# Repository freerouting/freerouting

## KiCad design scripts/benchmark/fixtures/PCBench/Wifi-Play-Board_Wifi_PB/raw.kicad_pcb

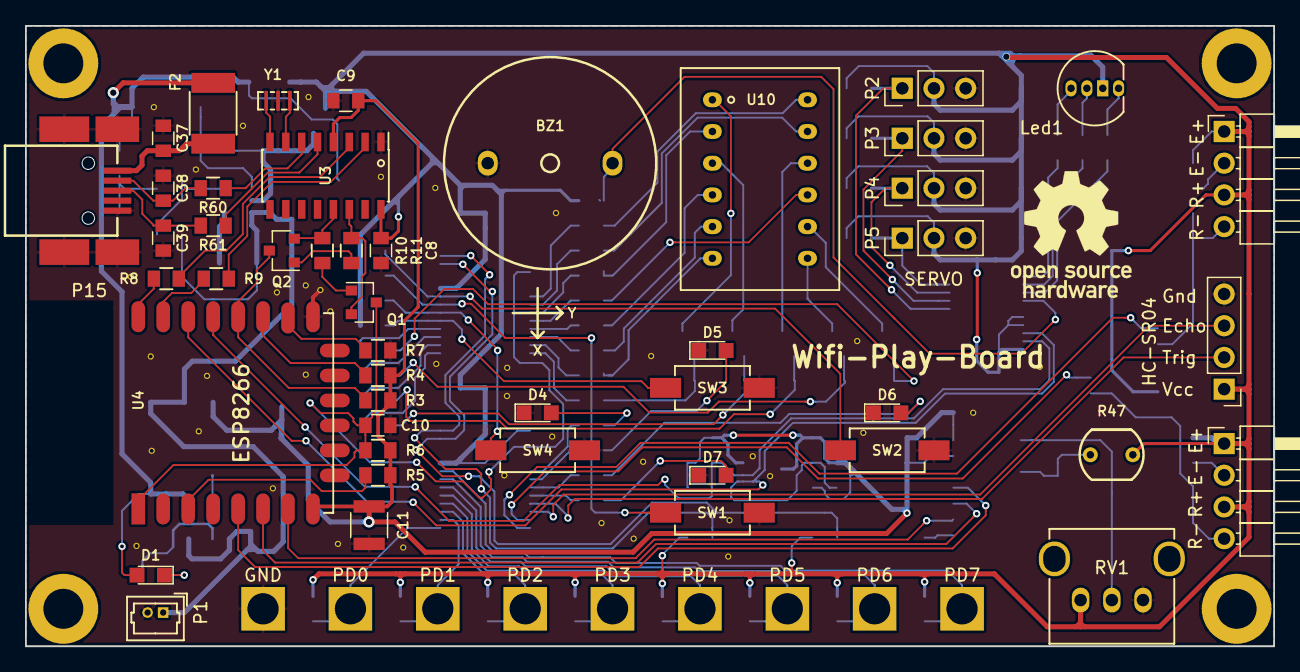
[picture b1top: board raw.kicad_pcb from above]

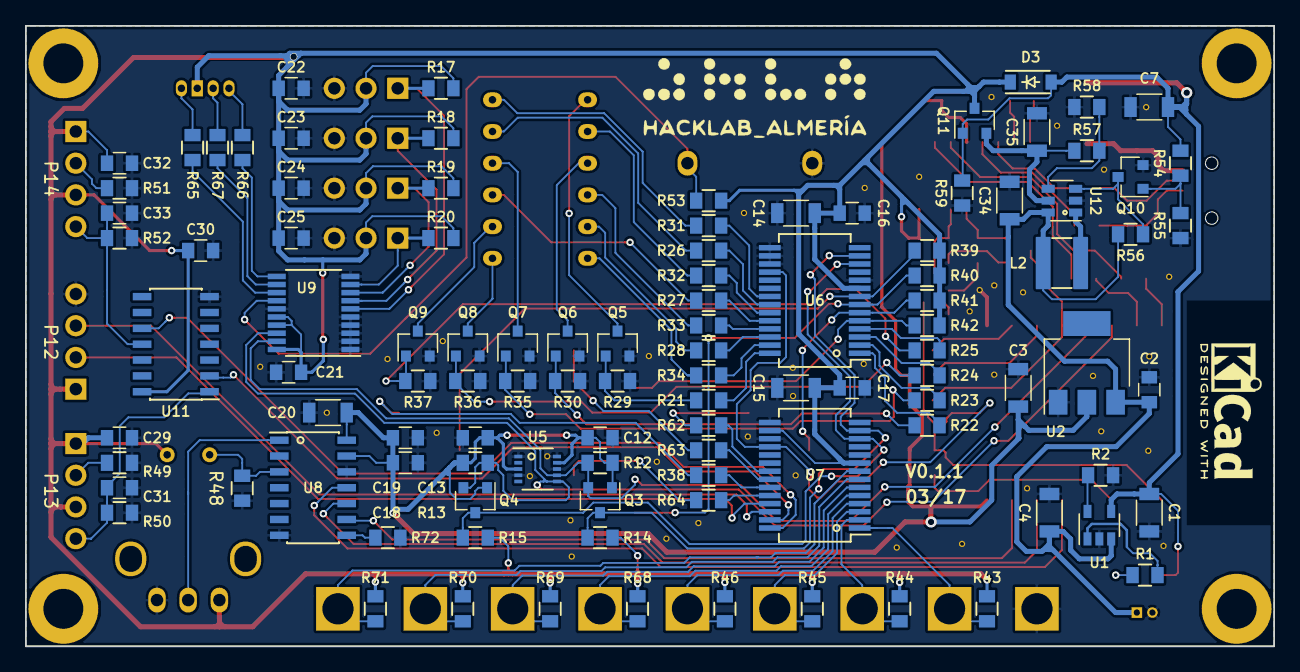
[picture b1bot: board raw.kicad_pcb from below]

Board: 2 copper layers, 100.0 x 49.7 mm, 200 parts (105 on the bottom side), 111 nets.

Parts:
BZ1: Buzzer; LOUDITY_LD-BZPN-1705
C1, C4, C14, C15, C20, C34: 4u7; C_1206
C2, C8, C9, C12, C13, C16, C17, C18, C19, C21, C29, C30, C32: 100n; C_0805
C3, C7, C35: 10u; C_1206
C10: 0.47n; C_0805
C11: 100u; C_1210
C22, C23, C24, C25: 1u; C_0805
C31, C33, C37: 10n; C_0805
C38, C39: 0,047n; C_0805
D1, D4, D5, D6, D7: LED; LED_0805
D3: MBR0520; SOD-123
F2: F; R_1812
Gnd-Via: VAL**; Gnd-Via
Gnd-Via#2, Gnd-Via#3, Gnd-Via#4, Gnd-Via#5, Gnd-Via#6, Gnd-Via#7, Gnd-Via#8, Gnd-Via#9, Gnd-Via#10, Gnd-Via#11, Gnd-Via#12, Gnd-Via#13, Gnd-Via#14, Gnd-Via#15, Gnd-Via#16, Gnd-Via#17, Gnd-Via#18, Gnd-Via#19, Gnd-Via#20, Gnd-Via#21, Gnd-Via#22, Gnd-Via#23, Gnd-Via#24, Gnd-Via#25, Gnd-Via#26, Gnd-Via#27, Gnd-Via#28, Gnd-Via#29, Gnd-Via#30, Gnd-Via#31, Gnd-Via#32, Gnd-Via#33, Gnd-Via#34, Gnd-Via#35, Gnd-Via#36, Gnd-Via#37, Gnd-Via#38, Gnd-Via#39: VAL**; Gnd-Via
L2: 4u7; BOURNS_SRN4012T
Led1: Led_RGB; LED_RGB_5mm_G_B_COM_R_Anodo_comun
P1: CONN_01X02; Molex_PicoBlade_53047-0210_02x1.25mm_Straight
P2, P3, P4, P5: CONN_01X03; Pin_Header_Straight_1x03_Pitch2.54mm
P6, P7, P8, P9, P10, P16, P17, P18, P19: CONN_01X01; Pad_Conector_Cocodrilo
P12: CONN_01X04; Socket_Strip_Straight_1x04_Pitch2.54mm
P13, P14: CONN_01X04; Pin_Header_Angled_1x04_Pitch2.54mm
P15: USB_MINI; usb_mini_molex_675031020
Q1, Q2, Q5, Q6, Q7, Q8, Q9: SMBT3904; SOT-23
Q3, Q4: BSS138; SOT-23
Q10: BC849; SOT-23
Q11: NX2301P; SOT-23
R1, R2, R8, R9: 470; R_0805
R3, R4, R5, R6, R7, R10, R11, R17, R18, R19, R20, R39, R40, R41, R42, R53, R56, R59: 10K; R_0805
R12, R13, R14, R15: 4K7; R_0805
R21, R22, R23, R24, R25, R48, R54: 1K; R_0805
R26, R27, R28, R31, R32, R33, R34, R65, R66, R67: 120; R_0805
R29, R30, R35, R36, R37, R50, R52, R55, R72: 47K; R_0805
R38, R62, R63, R64: 220; R_0805
R43, R44, R45, R46, R68, R69, R70, R71: 10M; R_0805
R47: LDR; LDR_TOKEN_PGM5_Series
R49, R51: 220R; R_0805
R57: 976K; R_0805
R58: 309K; R_0805
R60, R61: 22R; R_0805
RV1: POT; ALP_RK09K111
SW1, SW2, SW3, SW4: Pulsador_2p; CANAL_ELECTRONIC_DTSM-31N-B
U1: MCP73831T; SOT-23-5
U2: LD1117S33TR; SOT-223
U3: CH340G; SOIC-16_3.9x9.9mm_Pitch1.27mm
U4: ESP8266; ESP-12E
U5: MMA7660FC; DFN-10-1EP_3x3mm_Pitch0.5mm
U6, U7: MCP23017; SSOP-28_5.3x10.2mm_Pitch0.65mm
U8: MCP3204; SOIC-14_3.9x8.7mm_Pitch1.27mm
U9: PCA9634; TSSOP-20_4.4x6.5mm_Pitch0.65mm
U10: Matriz_5x7_Anodo_Filas; Matriz_Led_7X5
U11: 40106; SOIC-14_3.9x8.7mm_Pitch1.27mm
U12: MCP1640; SOT-23-6
Y1: Cristal; Murata_CSTCE_V_A

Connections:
+3V3: C3.1, C9.1, C11.1, C12.1, C13.1, C18.1, C19.1, C20.1, Q3.1, Q4.1, R3.2, R4.2, R5.2, R6.2, R12.1, R13.1, U2.2, U3.4, U4.8, U5.3, U5.9, U8.13, U8.14
+5V: C8.1, C14.1, C15.1, C16.1, C17.1, C21.1, C22.1, C23.1, C24.1, C25.1, C29.1, C30.1, C32.1, D3.1, Led1.3, P2.2, P3.2, P4.2, P5.2, P12.1, P13.1, P13.3, P14.1, P14.3, Q11.3, R14.1, R15.1, R17.1, R18.1, R19.1, R20.1, R39.1, R40.1, R41.1, R42.1, R43.1, R44.1, R45.1, R46.1, R47.1, R53.1, R68.1, R69.1, R70.1, R71.1, RV1.1, U3.16, U6.9, U7.9, U7.16, U9.16, U9.17, U9.20, U11.14
/Control/EN: R5.1, U4.3
/Control/GPIO0: Q2.3, R3.1, U4.18
/Control/GPIO2: R4.1, U4.17
/Control/GPIO15: R7.1, U4.16
/Control/RxD: R9.1, U4.21
/Control/TxD: R8.1, U4.22
/Control/USBD+: R61.1, U3.5
/Control/USBD-: R60.1, U3.6
BUZZER: BZ1.1, R53.2, U9.14
CH0: RV1.2, U8.1
CH2: R47.2, R48.2, U8.3
GND: BZ1.2, C1.2, C2.2, C3.2, C4.2, C7.2, C8.2, C9.2, C10.2, C11.2, C12.2, C13.2, C14.2, C15.2, C16.2, C17.2, C18.2, C19.2, C20.2, C21.2, C22.2, C23.2, C24.2, C25.2, C29.2, C30.2, C31.2, C32.2, C33.2, C34.2, C35.2, C37.2, C38.2, C39.2, D4.1, D5.1, D6.1, D7.1, Gnd-Via.1, Gnd-Via#2.1, Gnd-Via#3.1, Gnd-Via#4.1, Gnd-Via#5.1, Gnd-Via#6.1, Gnd-Via#7.1, Gnd-Via#8.1, Gnd-Via#9.1, Gnd-Via#10.1, Gnd-Via#11.1, Gnd-Via#12.1, Gnd-Via#13.1, Gnd-Via#14.1, Gnd-Via#15.1, Gnd-Via#16.1, Gnd-Via#17.1, Gnd-Via#18.1, Gnd-Via#19.1, Gnd-Via#20.1, Gnd-Via#21.1, Gnd-Via#22.1, Gnd-Via#23.1, Gnd-Via#24.1, Gnd-Via#25.1, Gnd-Via#26.1, Gnd-Via#27.1, Gnd-Via#28.1, Gnd-Via#29.1, Gnd-Via#30.1, Gnd-Via#31.1, Gnd-Via#32.1, Gnd-Via#33.1, Gnd-Via#34.1, Gnd-Via#35.1, Gnd-Via#36.1, Gnd-Via#37.1, Gnd-Via#38.1, Gnd-Via#39.1, P1.2, P2.3, P3.3, P4.3, P5.3, P10.1, P12.4, P15.5, P15.6, Q5.2, Q6.2, Q7.2, Q8.2, Q9.2, Q10.2, R2.2, R7.2, R29.2, R30.2, R35.2, R36.2, R37.2, R48.1, R49.2, R50.2, R51.2, R52.2, R55.2, R58.2, R59.1, R72.2, RV1.3, SW1.1, SW2.1, SW3.1, SW4.1, U1.2, U2.1, U3.1, U4.15, U5.1, U5.4, U5.8, U5.10, U6.10, U6.15, U6.16, U6.17, U7.10, U7.15, U7.17, U8.7, U8.12, U9.1, U9.2, U9.3, U9.4, U9.5, U9.10, U9.15, U11.7, U12.2, Y1.2
LED_BLUE: R67.2, U9.12
LED_GREEN: R66.2, U9.11
LED_RED: R65.2, U9.13
MISO: U4.6, U8.10
MOSI: U4.7, U8.9
unnamed: C31.1, P13.4, R50.1, U11.1
unnamed: C33.1, P14.4, R52.1, U11.11
unnamed: C37.1, F2.2, P15.1
unnamed: C38.1, P15.2, R60.2
unnamed: C39.1, P15.3, R61.2
unnamed: D1.1, R1.2
unnamed: D4.2, R62.2
unnamed: D5.2, R63.2
unnamed: D6.2, R38.2
unnamed: D7.2, R64.2
unnamed: L2.2, U12.1
unnamed: Led1.1, R66.1
unnamed: Led1.2, R67.1
unnamed: Led1.4, R65.1
unnamed: P13.2, R49.1
unnamed: P14.2, R51.1
unnamed: Q1.1, R10.1
unnamed: Q1.2, R11.2, U3.14
unnamed: Q2.1, R11.1
unnamed: Q2.2, R10.2, U3.13
unnamed: Q5.1, R21.1, R29.1
unnamed: Q5.3, U10.1
unnamed: Q6.1, R22.1, R30.1
unnamed: Q6.3, U10.3
unnamed: Q7.1, R23.1, R35.1
unnamed: Q7.3, U10.10
unnamed: Q8.1, R24.1, R36.1
unnamed: Q8.3, U10.7
unnamed: Q9.1, R25.1, R37.1
unnamed: Q9.3, U10.8
unnamed: Q10.1, R54.1, R55.1
unnamed: Q10.3, R56.1, U12.3
unnamed: R1.1, U1.1
unnamed: R2.1, U1.5
unnamed: R8.2, U3.3
unnamed: R9.2, U3.2
unnamed: R26.1, U10.11
unnamed: R27.1, U10.9
unnamed: R28.1, U10.5
unnamed: R31.1, U10.12
unnamed: R32.1, U10.2
unnamed: R33.1, U10.4
unnamed: R34.1, U10.6
unnamed: R57.2, R58.1, U12.4
unnamed: R72.1, U8.8
unnamed: U3.7, Y1.1
unnamed: U3.8, Y1.3
PA0: R31.2, U6.21
PA1: R26.2, U6.22
PA2: R32.2, U6.23
PA3: R27.2, U6.24
PA4: R33.2, U6.25
PA5: R28.2, U6.26
PA6: R34.2, U6.27
PA7: R21.2, U6.28
PB0: R22.2, U6.1
PB1: R23.2, U6.2
PB2: R24.2, U6.3
PB3: R25.2, U6.4
PB4: R42.2, SW3.2, U6.5
PB5: R41.2, SW4.2, U6.6
PB6: R40.2, SW1.2, U6.7
PB7: R39.2, SW2.2, U6.8
PC0: R62.1, U7.21
PC1: R63.1, U7.22
PC2: R38.1, U7.23
PC3: R64.1, U7.24
PC4: P12.2, U7.25
PC5: P12.3, U7.26
PC6: U7.27, U11.2
PC7: U7.28, U11.10
PD0: P6.1, R43.2, U7.1
PD1: P7.1, R44.2, U7.2
PD2: P8.1, R45.2, U7.3
PD3: P9.1, R46.2, U7.4
PD4: P16.1, R68.2, U7.5
PD5: P17.1, R69.2, U7.6
PD6: P18.1, R70.2, U7.7
PD7: P19.1, R71.2, U7.8
SCK: U4.5, U8.11
SCL: Q4.2, R13.2, U4.20, U5.6, U9.18
SCL2: Q4.3, R15.2, U6.12, U7.12
SDA: Q3.2, R12.2, U4.19, U5.7, U9.19
SDA2: Q3.3, R14.2, U6.13, U7.13
SERVO1: P2.1, R17.2, U9.6
SERVO2: P3.1, R18.2, U9.7
SERVO3: P4.1, R19.2, U9.8
SERVO4: P5.1, R20.2, U9.9
V5VBOOST: C35.1, Q11.2, R57.1, U12.5
VBATT: C2.1, C4.1, C34.1, L2.1, P1.1, R56.2, U1.3, U2.3, U12.6
VUSB: C1.1, C7.1, D1.2, D3.2, F2.1, Q11.1, R54.2, R59.2, U1.4
~RESET: C10.1, Q1.3, R6.1, U4.1, U6.18, U7.18

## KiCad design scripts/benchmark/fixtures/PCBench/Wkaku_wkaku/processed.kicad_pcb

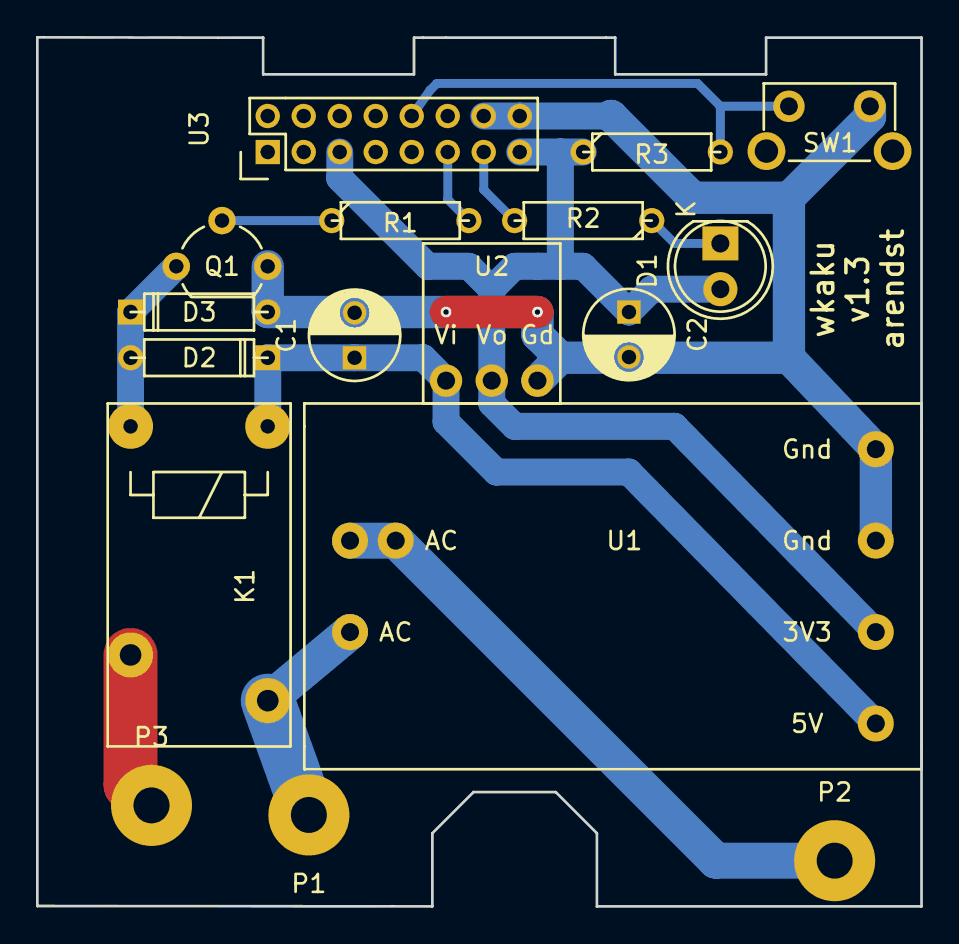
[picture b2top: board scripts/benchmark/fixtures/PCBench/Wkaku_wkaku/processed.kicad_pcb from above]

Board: 2 copper layers, 49.1 x 48.3 mm, 17 parts (0 on the bottom side), 12 nets.

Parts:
C1, C2: 100uF; C_Radial_D5_L11_P2.5
D1: LED; LED-5MM
D2, D3: 1N4007; D3
K1: RELAY_SPST; Relay_SPST
P1: Li; SolderWirePad_single_2mmDrill
P2: N; SolderWirePad_single_2mmDrill
P3: Lo; SolderWirePad_single_2mmDrill
Q1: BC547; TO-92_Molded_Wide
R1, R2: 1k; R3
R3: 10k; R3
SW1: SPST; SW_Tactile_SPST_Angled
U1: ACDC_Opt2; ACDC_Options
U2: AMS1117
U3: ESP-12E; ESP-12_Pitch2.00mm

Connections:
+3V3: C2.1, D1.2, R3.1, U1.4, U2.2, U3.3, U3.8
+5V: C1.1, D2.1, K1.A1, U1.3, U2.3
/BUTTON: R3.2, SW1.1, U3.18
/LED: R2.2, U3.7
/LIFE: K1.7, P1.1, U1.1
/RELAY: R1.2, U3.6
GND: C1.2, C2.2, D3.2, Q1.3, SW1.2, U1.5, U1.6, U2.1, U3.15, U3.16
unnamed: D1.1, R2.1
unnamed: D2.2, D3.1, K1.A2, Q1.1
unnamed: K1.5, P3.1
unnamed: P2.1, U1.2, U1.7
unnamed: Q1.2, R1.1

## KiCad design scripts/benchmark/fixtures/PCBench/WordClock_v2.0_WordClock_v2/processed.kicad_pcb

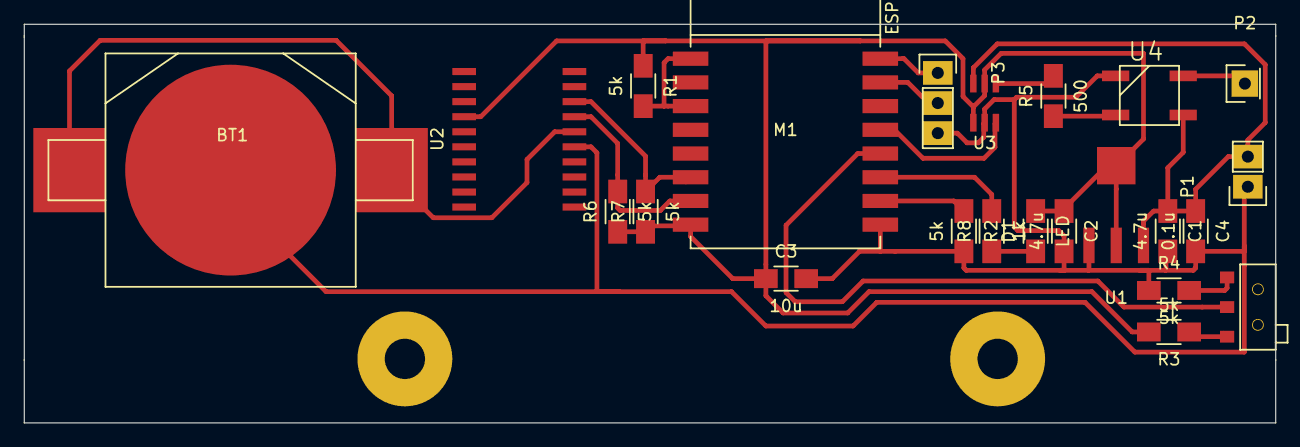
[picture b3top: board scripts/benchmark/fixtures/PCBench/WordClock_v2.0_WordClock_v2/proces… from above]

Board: 2 copper layers, 105.5 x 33.6 mm, 23 parts (0 on the bottom side), 19 nets.

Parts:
BT1: Battery; Battery_Holder_Cell_20mm_smd
C1, C2: 4.7u; C_1206_HandSoldering_IainEdit
C3: 10u; C_1206_HandSoldering_IainEdit
C4: 0.1u; C_1206_HandSoldering_IainEdit
D1: LED; C_1206_HandSoldering_IainEdit
M1: ESP-07
P1: 5V_input; Socket_Strip_Straight_1x02
P2: WS2812b_Out; Socket_Strip_Straight_1x01
P3: UART; Socket_Strip_Straight_1x03_IainEdit
R1, R2, R3, R4, R6, R7: 5k; C_1206_HandSoldering_IainEdit
R5: 500; C_1206_HandSoldering_IainEdit
R8: 1k; C_1206_HandSoldering_IainEdit
SW1: SWITCH_INV; SlideSwitch_smd
U1: NCP1117ST33T3G; SOT223_HandSolder
U2: DS3232; Maxim_SOIC-20_W20-H2
U3: SN74LVC1T45; TI-DBV-SOT23_handsolder
U4: WS2812b; WS2812b_handsolder

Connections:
+3V3: C2.1, C3.1, D1.2, M1.8, R1.1, R3.2, R6.1, R7.1, U1.2, U2.4, U3.1, U3.5
+5VD: C1.1, C4.1, P1.2, U1.3, U3.6, U4.1
GND: BT1.2, C1.2, C2.2, C3.2, C4.2, M1.9, P1.1, P3.3, R2.2, R4.1, U1.1, U2.15, U3.2, U4.3
GPIO0: M1.12, SW1.2
LED: M1.11, R8.2
unnamed: BT1.1, U2.16
unnamed: D1.1, R8.1
unnamed: M1.1, M1.3, R1.2
unnamed: M1.10, R2.1
unnamed: P2.1, U4.2
unnamed: R3.1, SW1.1
unnamed: R4.2, SW1.3
unnamed: R5.1, U4.4
unnamed: R5.2, U3.4
SCL: M1.6, R7.2, U2.18
SDA: M1.7, R6.2, U2.17
UART_Rx: M1.15, P3.2
UART_Tx: M1.16, P3.1
WS2812b_In: M1.13, U3.3

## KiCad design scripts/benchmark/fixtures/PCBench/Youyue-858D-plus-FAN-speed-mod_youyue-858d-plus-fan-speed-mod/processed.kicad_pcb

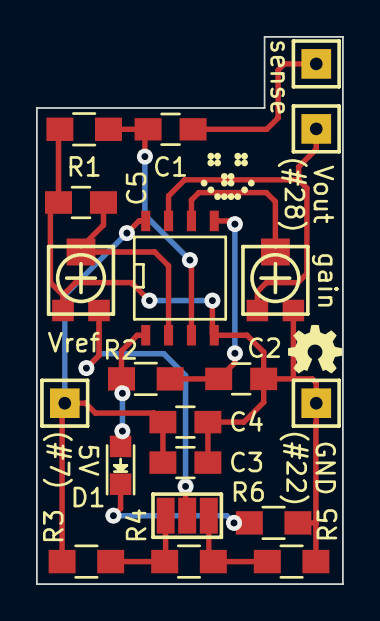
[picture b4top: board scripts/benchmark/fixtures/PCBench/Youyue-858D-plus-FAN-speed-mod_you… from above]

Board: 2 copper layers, 17.0 x 30.4 mm, 20 parts (0 on the bottom side), 13 nets.

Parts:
C1, C3: 100n; C_0805_HandSoldering
C2: 1µF; C_0805_HandSoldering
C4, C5: 1µ; C_0805_HandSoldering
D1: LED; LED-0805
JP1: SMD-JUMPER3; SMD-solder-bridge-3pin
P1, P2, P3, P4: CONN_01X01; SIL-1
R1: 1M; R_0805_HandSoldering
R2: 100k; R_0805_HandSoldering
R3: 10k; R_0805_HandSoldering
R4, R5: 390R; R_0805_HandSoldering
R6: 1k; R_0805_HandSoldering
RV1, RV2: 4k7; MADW__TC33X-POT
U1: LM2904; SOIC-8-N

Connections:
+5V: C3.1, C4.1, P3.1, R3.1, U1.8
/I_BLDC: C1.1, P1.1
/V_out: P2.1, RV2.1, U1.7
/V_ref: C5.1, RV1.2, U1.2
/comp_adj: D1.2, R2.2, U1.1
GND: C2.2, C3.2, C4.2, C5.2, P4.1, R1.2, R5.2, R6.2, RV1.1, RV2.3, U1.4
unnamed: C1.2, R1.1, U1.3
unnamed: C2.1, R2.1, U1.5
unnamed: D1.1, R6.1
unnamed: JP1.1, R4.2, R5.1
unnamed: JP1.2, RV1.3
unnamed: JP1.3, R3.2, R4.1
unnamed: RV2.2, U1.6
